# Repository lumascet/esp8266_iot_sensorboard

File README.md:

# Esp8266 IOT Sensorboard
A IOT Device with lots of sensors publishing acquired data via MQTT with automatic Home Assistant integration.
The board is equipped with following key components: 

* MQ Gas Sensors
    * MQ-3 Alcohol
    * MQ-4 CH4, LPG
    * MQ-7 CO
    * MQ-8 H2
    * MQ-135 Air-Quality
* BME280 Barometric Pressure, Temperature & Humidity
* GMYL8511 UV sensor
* GP2Y1010AU0F Sharp Dust Sensor
* Generic PIR Sensor
* Generic Microphone
* 5528 LDR
* PCF8574 I2C Port Expander
* ADS1115 16 bit ADC
* 74HC4051 8 channel Multiplexer

can be expanded with any other analog or i2c sensors.

Supports ESP8266 Boards NodeMCU & WeMos D1 mini

# Installation # 

just run the Platformio build task.

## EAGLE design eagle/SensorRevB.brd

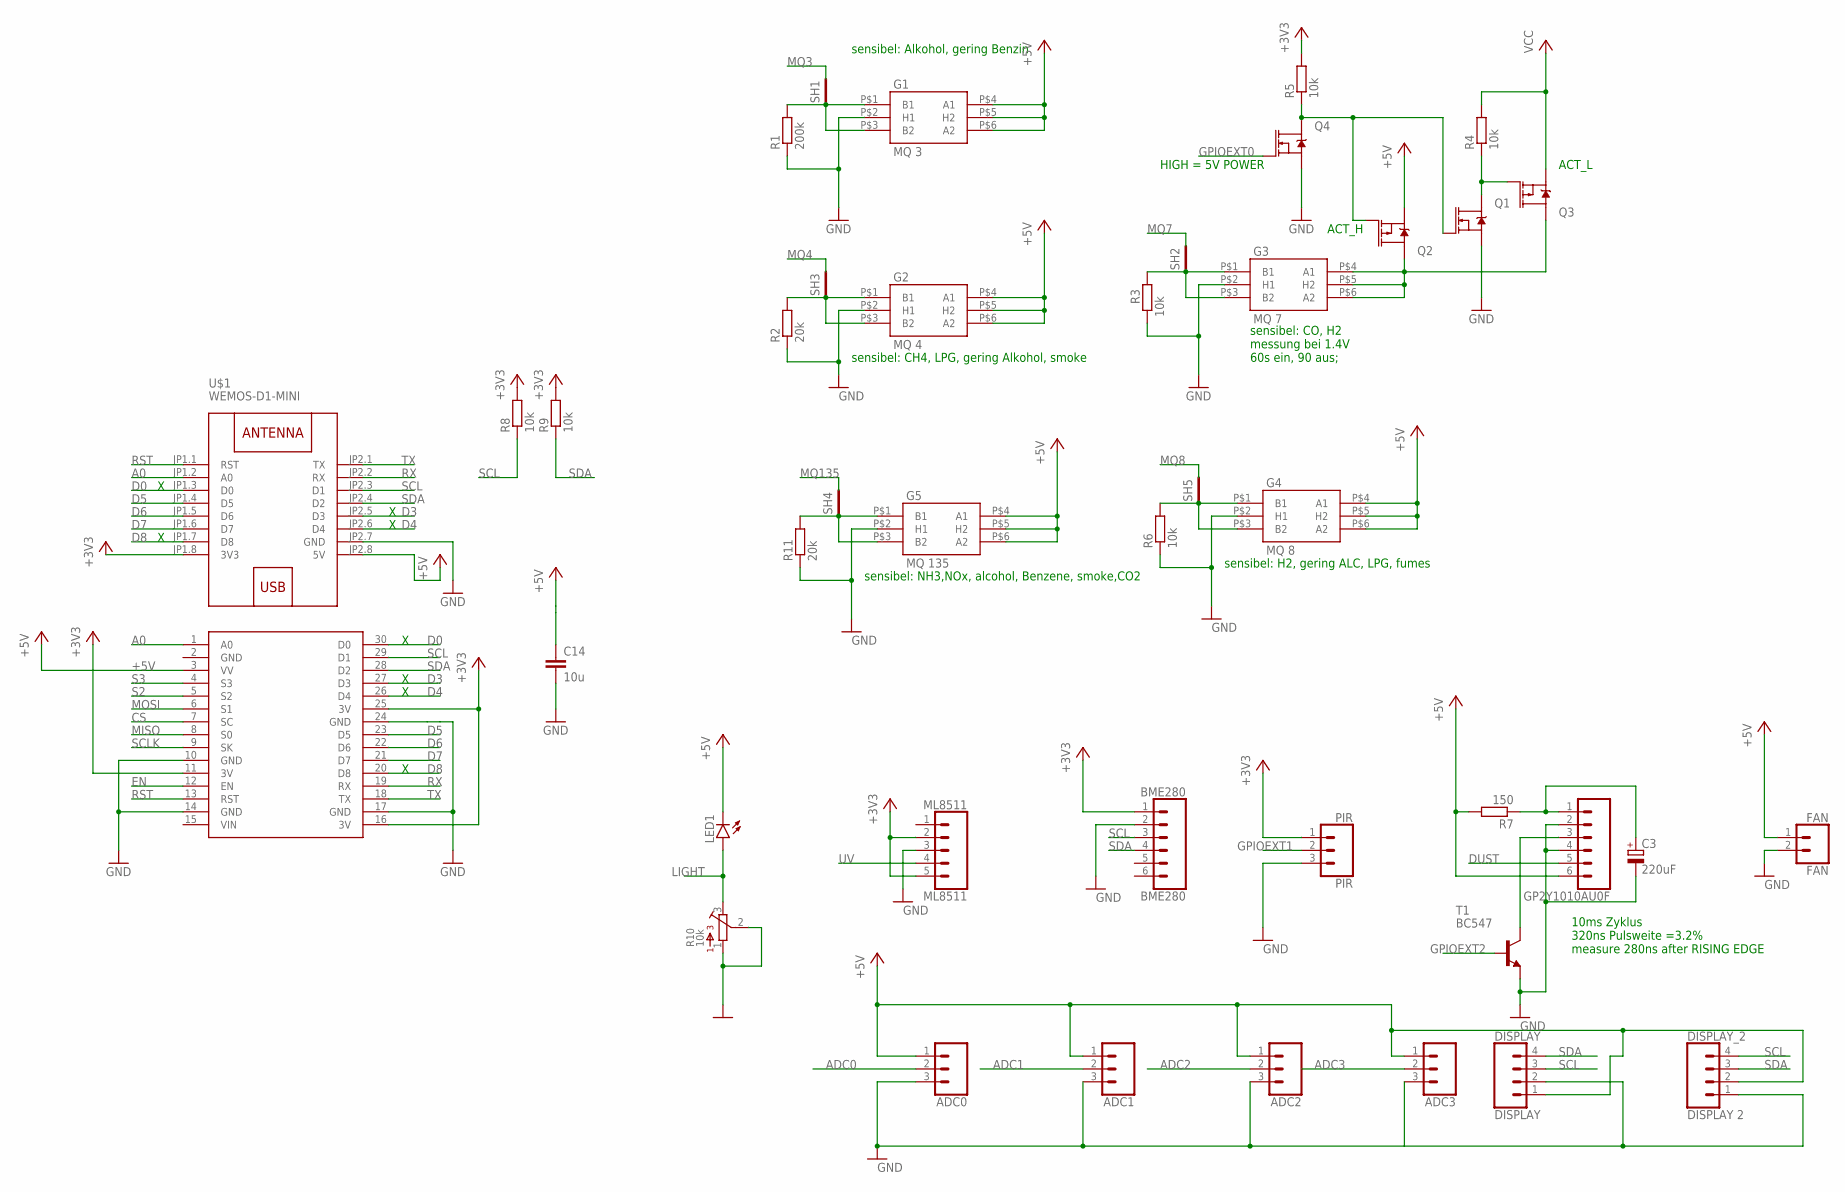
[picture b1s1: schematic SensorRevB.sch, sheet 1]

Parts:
ADC0, ADC1, ADC2, ADC3: CONN_03; 1X03
BME280: BME280; 1X06
C3: 220uF; E2-5
C14: 10u; C0603
DISPLAY: DISPLAY; 1X04
DISPLAY_2: DISPLAY 2; 1X04
FAN: FAN; 1X02_LOCK
G1: MQ 3; GAS_SOCKET
G2: MQ 4; GAS_SOCKET
G3: MQ 7; GAS_SOCKET
G4: MQ 8; GAS_SOCKET
G5: MQ 135; GAS_SOCKET
GP2Y1010AU0F: CONN_06SILK_FEMALE_PTH; 1X06
LED1: LED5MM
ML8511: ML8511; 1X05
PIR: PIR; 1X03_LOCK
Q1, Q4: 5.8A/30V/35mΩ; SOT23-3
Q2, Q3: 4.3A/20V/54mΩ; SOT23-3
R1: 200k; R0805
R2, R11: 20k; R0805
R3, R4, R5, R6, R8, R9: 10k; R0805
R7: 150; R0805
R10: 10k; 3362P
SH1, SH2, SH3, SH4, SH5: SHORT-HT5; SHORT_TOP-50
T1: BC547; TO92
U$1: WEMOS-D1-MINI
U$2: NODEMCU

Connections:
+3V3: BME280.1, ML8511.2, ML8511.5, PIR.1, R5.2, R8.2, R9.2, U$1.JP1.8 (3V3), U$2.11 (3V), U$2.16 (3V), U$2.25 (3V)
+5V: ADC0.1, ADC1.1, ADC2.1, ADC3.1, C14.1, DISPLAY.1, DISPLAY_2.2, FAN.1, G1.P$4 (A1), G1.P$5 (H2), G1.P$6 (A2), G2.P$4 (A1), G2.P$5 (H2), G2.P$6 (A2), G4.P$4 (A1), G4.P$5 (H2), G4.P$6 (A2), G5.P$4 (A1), G5.P$5 (H2), G5.P$6 (A2), GP2Y1010AU0F.6, LED1.K (C), Q2.2 (S), R7.2, U$1.JP2.8 (5V), U$2.3 (VV); also elsewhere on the board
A0: U$1.JP1.2 (A0), U$2.1 (A0)
ADC0: ADC0.2; also elsewhere on the board
ADC1: ADC1.2; also elsewhere on the board
ADC2: ADC2.2; also elsewhere on the board
ADC3: ADC3.2; also elsewhere on the board
CS: U$2.7 (SC)
D0: U$1.JP1.3 (D0), U$2.30 (D0)
D3: U$1.JP2.5 (D3), U$2.27 (D3)
D4: U$1.JP2.6 (D4), U$2.26 (D4)
D5: U$1.JP1.4 (D5), U$2.23 (D5); also elsewhere on the board
D6: U$1.JP1.5 (D6), U$2.22 (D6)
D7: U$1.JP1.6 (D7), U$2.21 (D7)
D8: U$1.JP1.7 (D8), U$2.20 (D8)
DUST: GP2Y1010AU0F.5; also elsewhere on the board
EN: U$2.12 (EN)
GND: ADC0.3, ADC1.3, ADC2.3, ADC3.3, BME280.2, C3.-, C14.2, DISPLAY.2, DISPLAY_2.1, FAN.2, G1.P$2 (H1), G2.P$2 (H1), G3.P$2 (H1), G4.P$2 (H1), G5.P$2 (H1), GP2Y1010AU0F.2, GP2Y1010AU0F.4, ML8511.3, PIR.3, Q1.2 (S), Q4.2 (S), R1.1, R2.1, R3.1, R6.1, R10.1, R10.2, R11.1, T1.1 (E), U$1.JP2.7 (GND), U$2.2 (GND), U$2.10 (GND), U$2.14 (GND), U$2.17 (GND), U$2.24 (GND); also elsewhere on the board
GPIOEXT0: Q4.1 (G); also elsewhere on the board
GPIOEXT1: PIR.2; also elsewhere on the board
GPIOEXT2: T1.2 (B); also elsewhere on the board
LIGHT: LED1.A, R10.3; also elsewhere on the board
MISO: U$2.8 (S0)
MOSI: U$2.6 (S1)
MQ3: SH1.2; also elsewhere on the board
MQ4: SH3.2; also elsewhere on the board
MQ7: SH2.2; also elsewhere on the board
MQ8: SH5.2; also elsewhere on the board
MQ135: SH4.2; also elsewhere on the board
unnamed: C3.+, GP2Y1010AU0F.1, R7.1
unnamed: GP2Y1010AU0F.3, T1.3 (C)
unnamed: Q1.3 (D), Q3.1 (G), R4.1
unnamed: Q1.1 (G), Q2.1 (G), Q4.3 (D), R5.1
unnamed: G1.P$1 (B1), G1.P$3 (B2), R1.2, SH1.1
unnamed: G3.P$4 (A1), G3.P$5 (H2), G3.P$6 (A2), Q2.3 (D), Q3.3 (D)
unnamed: G3.P$1 (B1), G3.P$3 (B2), R3.2, SH2.1
unnamed: G2.P$1 (B1), G2.P$3 (B2), R2.2, SH3.1
unnamed: G5.P$1 (B1), G5.P$3 (B2), R11.2, SH4.1
unnamed: G4.P$1 (B1), G4.P$3 (B2), R6.2, SH5.1
RST: U$1.JP1.1 (RST), U$2.13 (RST)
RX: U$1.JP2.2 (RX), U$2.19 (RX)
S2: U$2.5 (S2)
S3: U$2.4 (S3)
SCL: BME280.3, DISPLAY.3, DISPLAY_2.4, R8.1, U$1.JP2.3 (D1), U$2.29 (D1); also elsewhere on the board
SCLK: U$2.9 (SK)
SDA: BME280.4, DISPLAY.4, DISPLAY_2.3, R9.1, U$1.JP2.4 (D2), U$2.28 (D2); also elsewhere on the board
TX: U$1.JP2.1 (TX), U$2.18 (TX)
UV: ML8511.4; also elsewhere on the board
VCC: Q3.2 (S), R4.2; also elsewhere on the board

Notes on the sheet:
sensibel: Alkohol, gering Benzin
sensibel: CH4, LPG, gering Alkohol, smoke
sensibel: CO, H2 messung bei 1.4V 60s ein, 90 aus;
ACT_H
ACT_L
HIGH = 5V POWER
sensibel: H2, gering ALC, LPG, fumes
sensibel: NH3,NOx, alcohol, Benzene, smoke,CO2
10ms Zyklus 320ns Pulsweite =3.2% measure 280ns after RISING EDGE

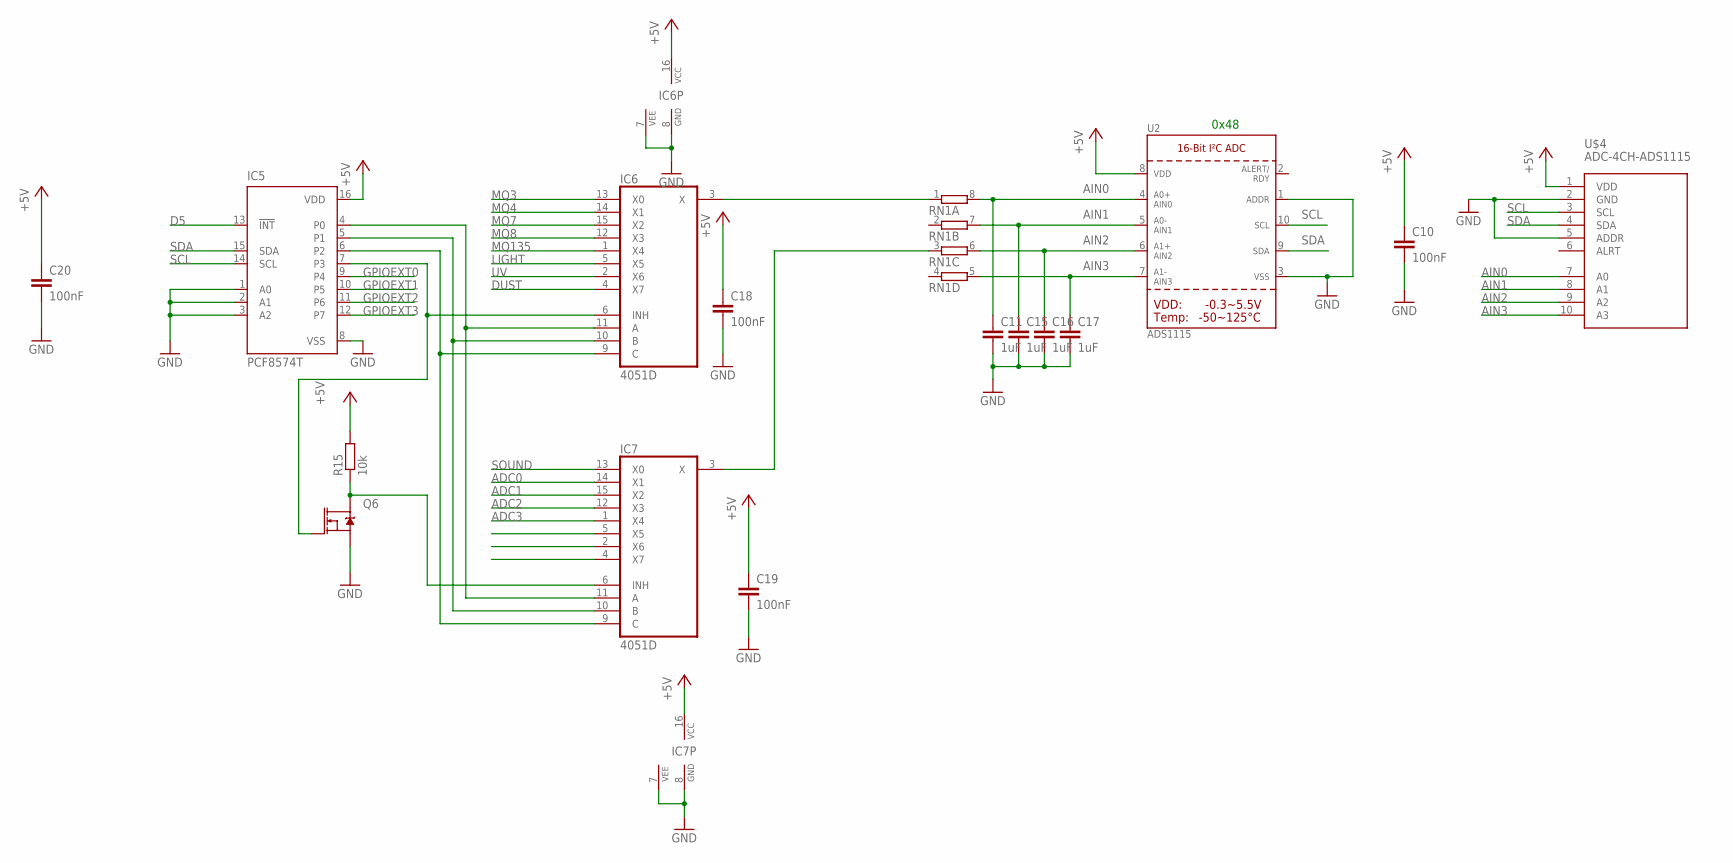
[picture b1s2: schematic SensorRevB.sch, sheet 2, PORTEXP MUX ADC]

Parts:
C10, C18, C19, C20: 100nF; C0603
C11, C15, C16, C17: 1uF; C0603
IC5: PCF8574T; SO16W
IC6, IC7: 4051D; SO16
Q6: 5.8A/30V/35mΩ; SOT23-3
R15: 10k; R0805
RN1: 4R-N0603-ARC; 0603-ARC
U2: ADS1115; MSOP10
U$4: ADC-4CH-ADS1115

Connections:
+5V: C10.1, C18.1, C19.1, C20.1, IC5.16 (VDD), IC6.16 (VCC), IC7.16 (VCC), R15.2, U2.8 (VDD), U$4.1 (VDD); also elsewhere on the board
ADC0: IC7.14 (X1); also elsewhere on the board
ADC1: IC7.15 (X2); also elsewhere on the board
ADC2: IC7.12 (X3); also elsewhere on the board
ADC3: IC7.1 (X4); also elsewhere on the board
AIN0: C11.1, RN1.8 (2), U2.4 (AIN0), U$4.7 (A0)
AIN1: C15.1, RN1.7 (2), U2.5 (AIN1), U$4.8 (A1)
AIN2: C16.1, RN1.6 (2), U2.6 (AIN2), U$4.9 (A2)
AIN3: C17.1, RN1.5 (2), U2.7 (AIN3), U$4.10 (A3)
D5: IC5.13 (!INT); also elsewhere on the board
DUST: IC6.4 (X7); also elsewhere on the board
GND: C10.2, C11.2, C15.2, C16.2, C17.2, C18.2, C19.2, C20.2, IC5.1 (A0), IC5.2 (A1), IC5.3 (A2), IC5.8 (VSS), IC6.7 (VEE), IC6.8 (GND), IC7.7 (VEE), IC7.8 (GND), Q6.2 (S), U2.1 (ADDR), U2.3 (VSS), U$4.2 (GND), U$4.5 (ADDR); also elsewhere on the board
GPIOEXT0: IC5.9 (P4); also elsewhere on the board
GPIOEXT1: IC5.10 (P5); also elsewhere on the board
GPIOEXT2: IC5.11 (P6); also elsewhere on the board
GPIOEXT3: IC5.12 (P7)
LIGHT: IC6.5 (X5); also elsewhere on the board
MQ3: IC6.13 (X0); also elsewhere on the board
MQ4: IC6.14 (X1); also elsewhere on the board
MQ7: IC6.15 (X2); also elsewhere on the board
MQ8: IC6.12 (X3); also elsewhere on the board
MQ135: IC6.1 (X4); also elsewhere on the board
unnamed: IC5.4 (P0), IC6.11 (A), IC7.11 (A)
unnamed: IC5.5 (P1), IC6.10 (B), IC7.10 (B)
unnamed: IC5.6 (P2), IC6.9 (C), IC7.9 (C)
unnamed: IC5.7 (P3), IC6.6 (INH), Q6.1 (G)
unnamed: IC7.6 (INH), Q6.3 (D), R15.1
unnamed: IC6.3 (X), RN1.1
unnamed: IC7.3 (X), RN1.3 (1)
SCL: IC5.14 (SCL), U2.10 (SCL), U$4.3 (SCL); also elsewhere on the board
SDA: IC5.15 (SDA), U2.9 (SDA), U$4.4 (SDA); also elsewhere on the board
SOUND: IC7.13 (X0); also elsewhere on the board
UV: IC6.2 (X6); also elsewhere on the board

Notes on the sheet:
0x48

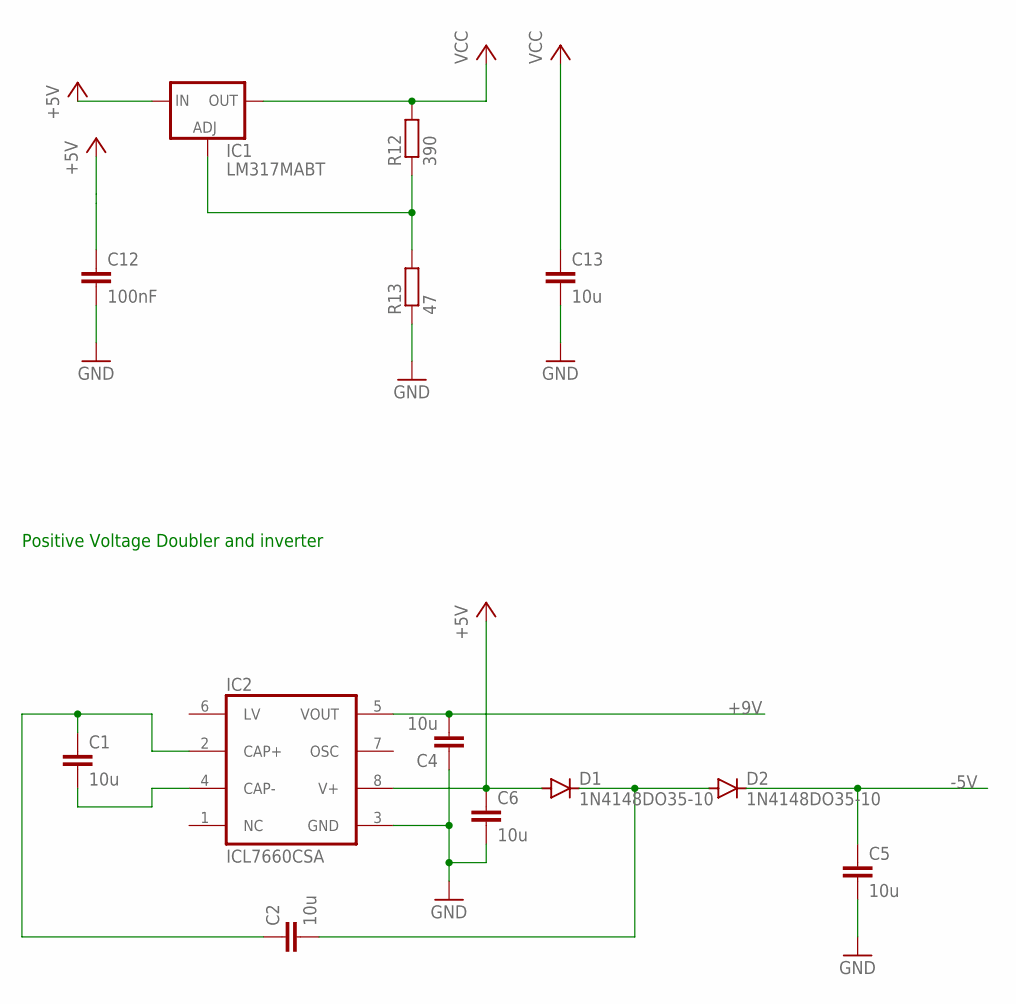
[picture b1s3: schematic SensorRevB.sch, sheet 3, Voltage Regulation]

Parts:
C1, C2, C4, C5, C6, C13: 10u; C0603
C12: 100nF; C0603
D1, D2: 1N4148DO35-10; DO35-10
IC1: LM317MABT; TO220L1
IC2: ICL7660CSA; SO08
R12: 390; R0805
R13: 47; R0805

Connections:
+5V: C6.1, C12.1, D1.A, IC1.3 (IN), IC2.8 (V+); also elsewhere on the board
+9V: C4.2, IC2.5 (VOUT); also elsewhere on the board
-5V: C5.1, D2.C; also elsewhere on the board
GND: C4.1, C5.2, C6.2, C12.2, C13.2, IC2.3 (GND), R13.1; also elsewhere on the board
unnamed: C1.1, C2.1, IC2.2 (CAP+)
unnamed: C1.2, IC2.4 (CAP-)
unnamed: IC1.1 (ADJ), R12.1, R13.2
unnamed: C2.2, D1.C, D2.A
VCC: C13.1, IC1.2 (OUT), R12.2; also elsewhere on the board

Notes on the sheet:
Positive Voltage Doubler and inverter

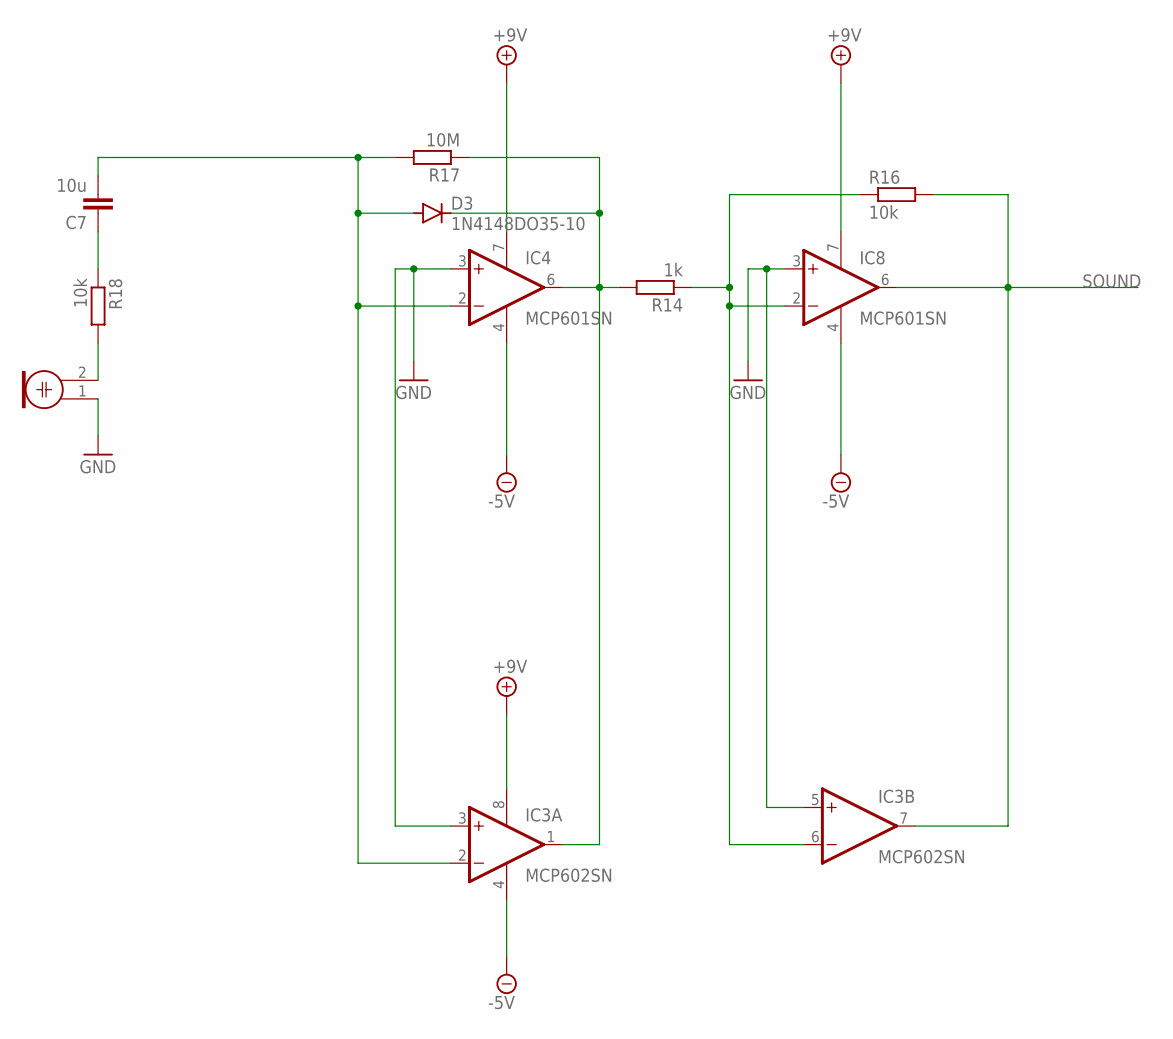
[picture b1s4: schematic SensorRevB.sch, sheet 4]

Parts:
C7: 10u; C0603
D3: 1N4148DO35-10; DO35-10
IC3: MCP602SN; SO08
IC4, IC8: MCP601SN; SO08
M1: ELECTRET_MICROPHON-WM-61B; WM-61B
R14: 1k; R0805
R16, R18: 10k; R0805
R17: 10M; R0805

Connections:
+9V: IC3.8 (V+), IC4.7 (V+), IC8.7 (V+); also elsewhere on the board
-5V: IC3.4 (V-), IC4.4 (V-), IC8.4 (V-); also elsewhere on the board
GND: IC3.3 (+IN), IC3.5 (+IN), IC4.3 (+IN), IC8.3 (+IN), M1.1; also elsewhere on the board
unnamed: IC3.6 (-IN), IC8.2 (-IN), R14.1, R16.1
unnamed: D3.C, IC3.1 (OUT), IC4.6 (OUT), R14.2, R17.1
unnamed: C7.1, R18.1
unnamed: C7.2, D3.A, IC3.2 (-IN), IC4.2 (-IN), R17.2
unnamed: M1.2, R18.2
SOUND: IC3.7 (OUT), IC8.6 (OUT), R16.2; also elsewhere on the board

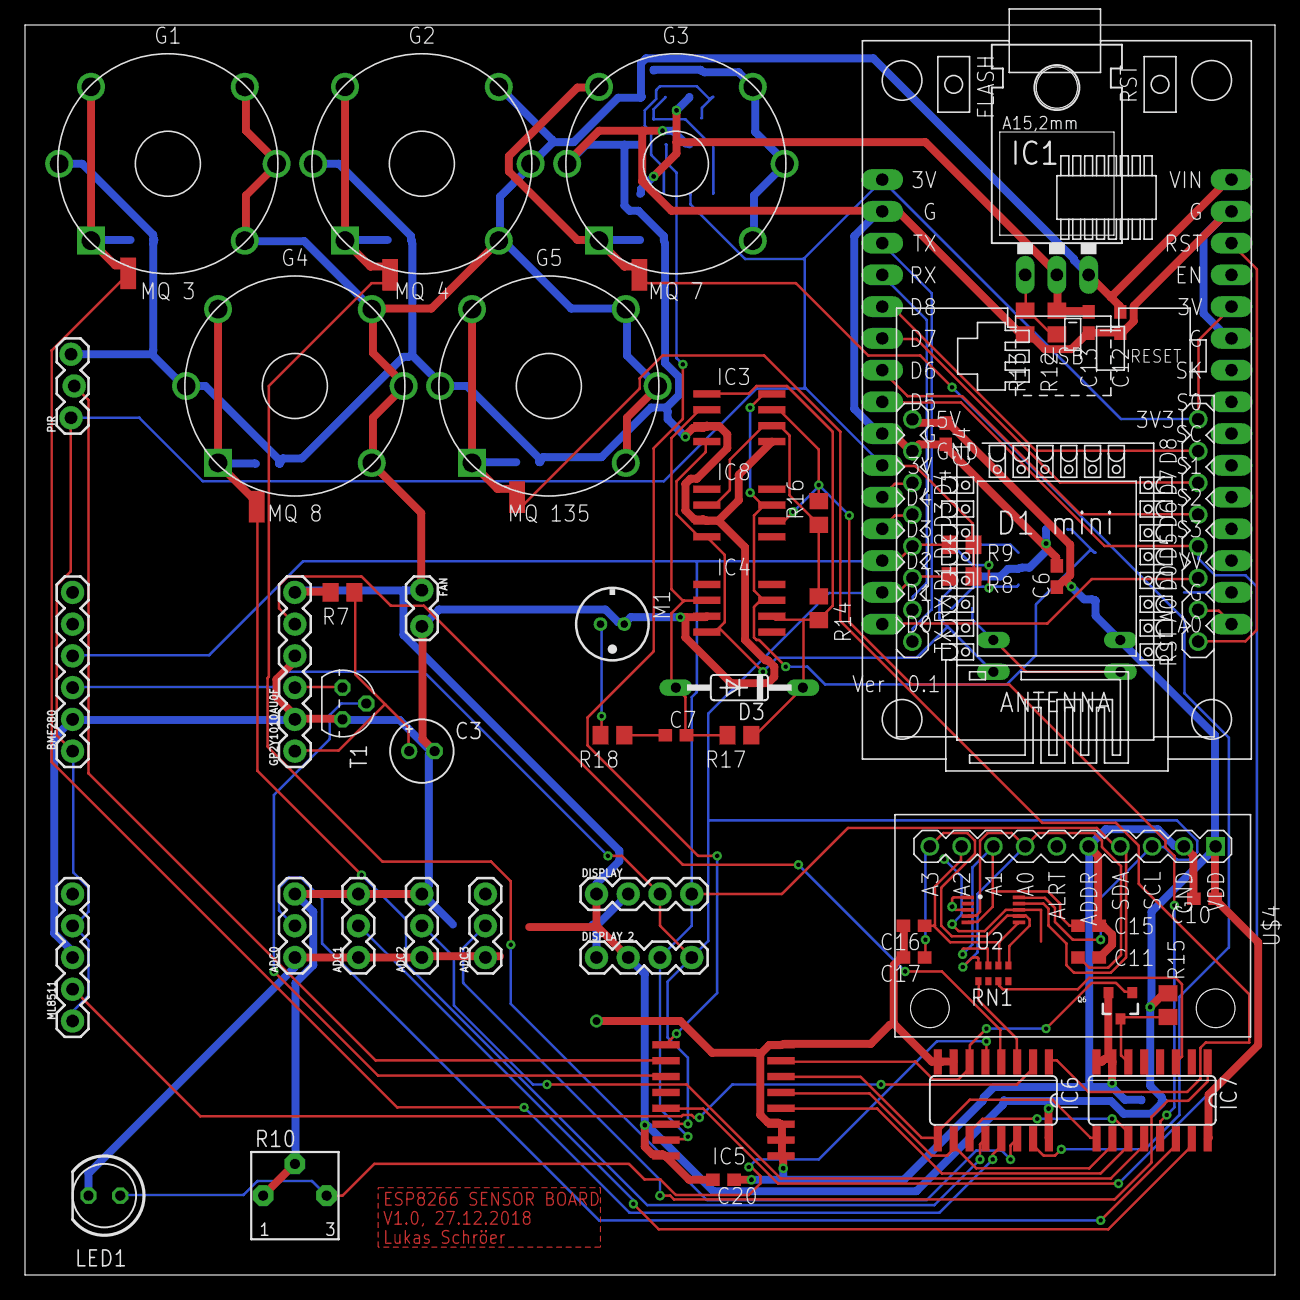
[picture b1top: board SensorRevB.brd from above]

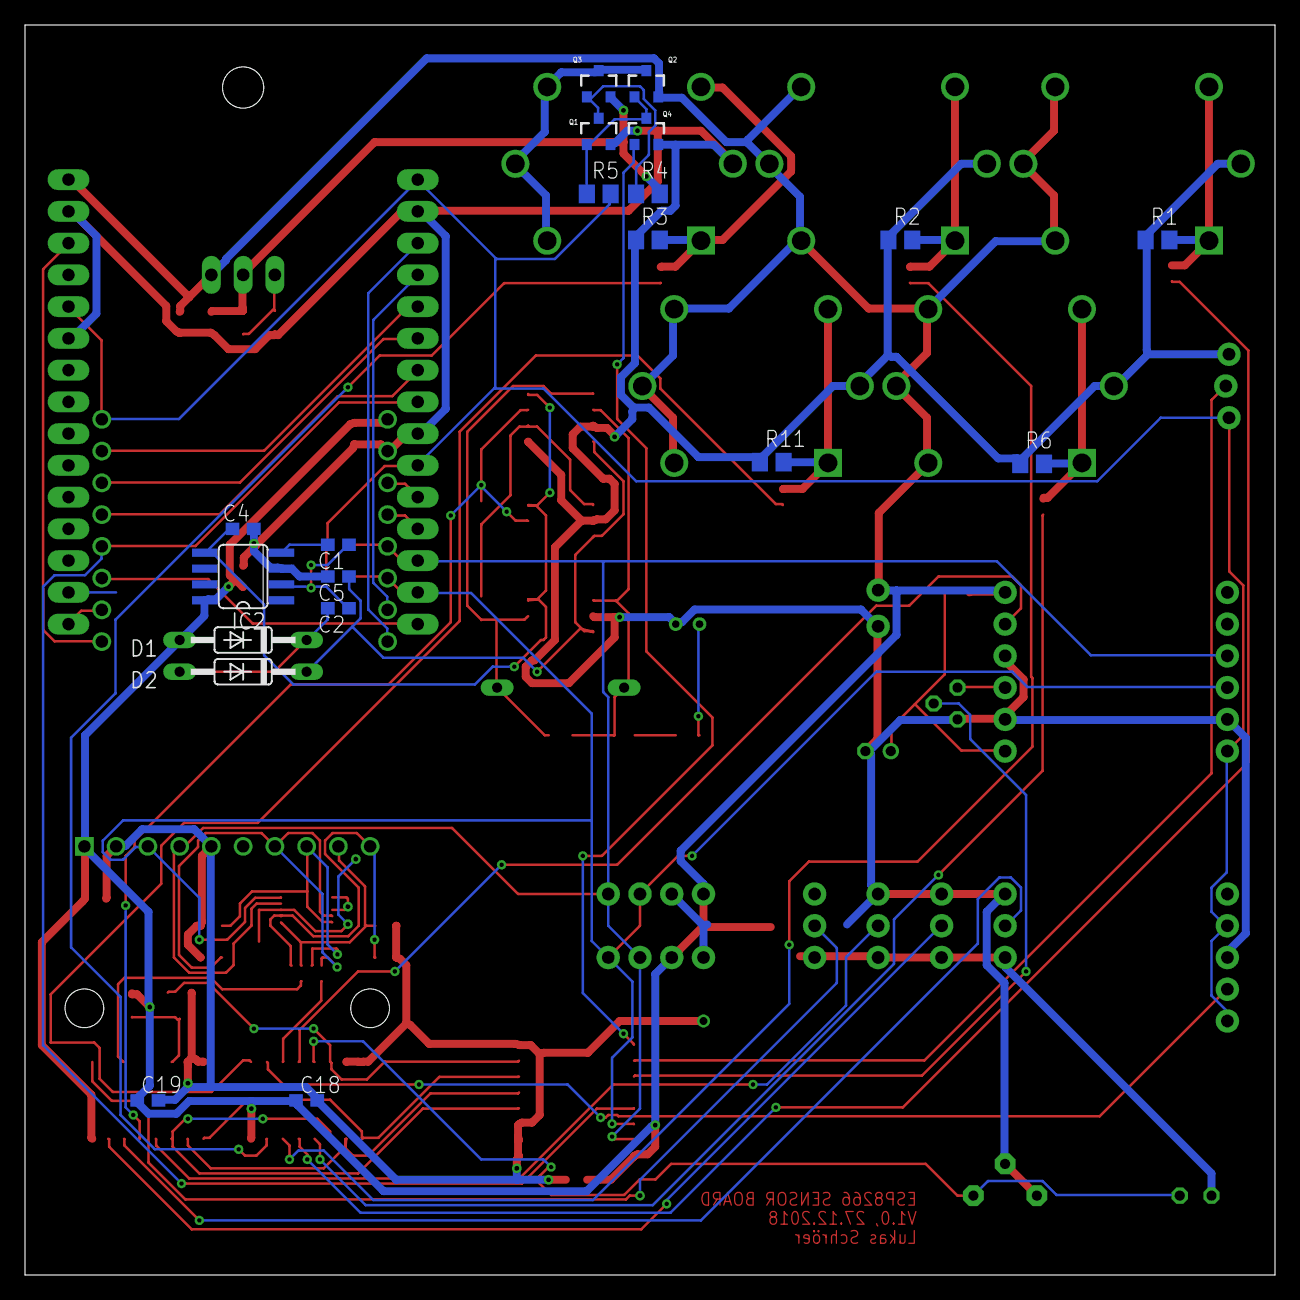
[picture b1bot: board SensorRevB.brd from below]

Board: 2 copper layers, 100.0 x 100.0 mm, 81 parts (20 on the bottom side), 65 nets.

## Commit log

2019-09-21 init
2019-09-21 added lib deps
2019-09-27 home assistant discovery, changed to PubSubMqtt
2019-09-27 changed lib
2019-09-28 fixed mqtt payload size to 2048
2019-09-28 bugfixes
2019-09-30 fixed allocation size
2019-09-30 fixed ip payload
2019-09-30 restart esp if startup connection takes long time
2020-01-19 changed board, added pcp schematics
2020-01-19 removed credential visibility
2020-01-19 added basic description
2020-01-19 additional information
2020-01-19 temp to lowercase
2020-01-19 fixed
2020-01-19 removed .vscodegit
2020-01-19 removed .vscode

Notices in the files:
parts and their libraries:
diy-modules: Released under the Creative Commons Attribution 4.0 International License: http://creativecommons.org/licenses/by/4.0
SparkFun-Connectors: Licensing: Creative Commons ShareAlike 4.0 International - https://creativecommons.org/licenses/by-sa/4.0
